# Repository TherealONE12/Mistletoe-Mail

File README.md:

# Mistletoe Mail

A Christmas Eve memory game for the [Holiday Hardware Swap](https://swap.hackclub.com/). Watch the bakery, post office and toy shop windows light up, then ring their doorbells in the same order. The route grows from two stops to six. Finish it to hear *Jingle Bells*.

## Play

- **Start a delivery:** Plug in USB and tap any doorbell. When all three windows glow dimly, repeat the route. A wrong turn replays it.
- **Quiet mode:** While idle, hold POST for a second and release to toggle sound on and off.
- **Music box:** Hold BAKERY and TOYS while plugging in, then release. The doors play C, E and G as notes.

## Hack it

On a Pico H running CircuitPython, copy [code.py](firmware/code.py) onto `CIRCUITPY`. Edit `CAROL` to edit the victory tune.

| Connection | Pico pins |
| --- | --- |
| Windows / doorbells, left to right | GP2, GP6, GP10 / GP4, GP8, GP12 |
| Piezo | GP14 |
| J1 expansion, top to bottom | 3V3, GP20 (SDA), GP21 (SCL), GND |

J1 accepts a 3.3 V I²C accessory with its own pull-ups.

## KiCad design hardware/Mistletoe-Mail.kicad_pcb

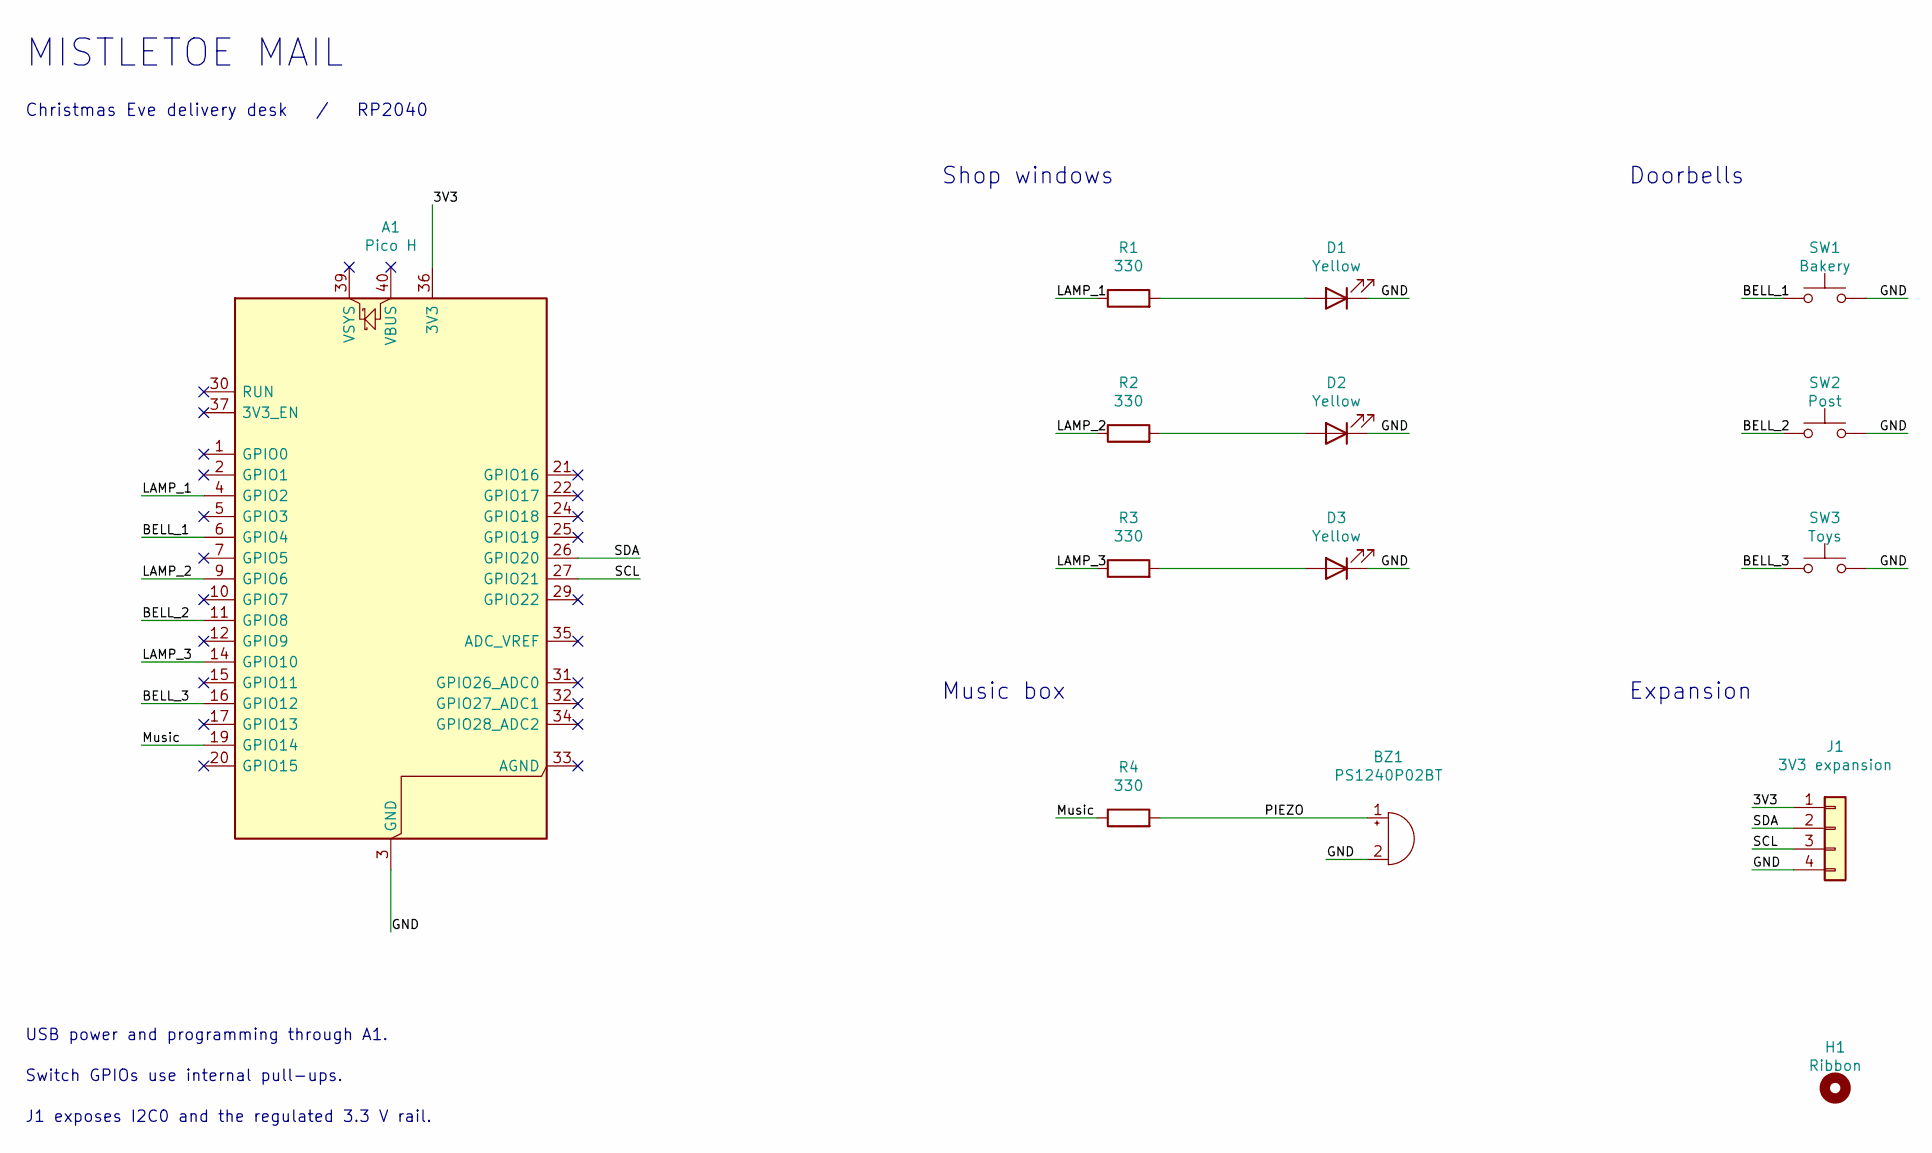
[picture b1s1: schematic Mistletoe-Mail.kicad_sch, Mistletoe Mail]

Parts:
A1: Pico H; Pico
BZ1: PS1240P02BT; Piezo
D1, D2, D3: Yellow; Window
H1: Ribbon; Eyelet
J1: 3V3 expansion; Port
R1, R2, R3, R4: 330; Resistor
SW1: Bakery; Doorbell
SW2: Post; Doorbell
SW3: Toys; Doorbell

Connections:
/3V3: A1.36 (3V3), J1.1
/ANODE_1: D1.2 (A), R1.2
/ANODE_2: D2.2 (A), R2.2
/ANODE_3: D3.2 (A), R3.2
/BELL_1: A1.6 (GPIO4), SW1.1
/BELL_2: A1.11 (GPIO8), SW2.1
/BELL_3: A1.16 (GPIO12), SW3.1
/CHIME: A1.19 (GPIO14), R4.1
/GND: A1.3 (GND), A1.8 (GND), A1.13 (GND), A1.18 (GND), A1.23 (GND), A1.28 (GND), A1.38 (GND), BZ1.2 (-), D1.1 (K), D2.1 (K), D3.1 (K), J1.4, SW1.2, SW2.2, SW3.2
/LAMP_1: A1.4 (GPIO2), R1.1
/LAMP_2: A1.9 (GPIO6), R2.1
/LAMP_3: A1.14 (GPIO10), R3.1
/PIEZO: BZ1.1 (+), R4.2
/SCL: A1.27 (GPIO21), J1.3
/SDA: A1.26 (GPIO20), J1.2

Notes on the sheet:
MISTLETOE MAIL
Christmas Eve delivery desk / RP2040
Expansion
Doorbells
Shop windows
USB power and programming through A1.
J1 exposes I2C0 and the regulated 3.3 V rail.
Music box
Switch GPIOs use internal pull-ups.

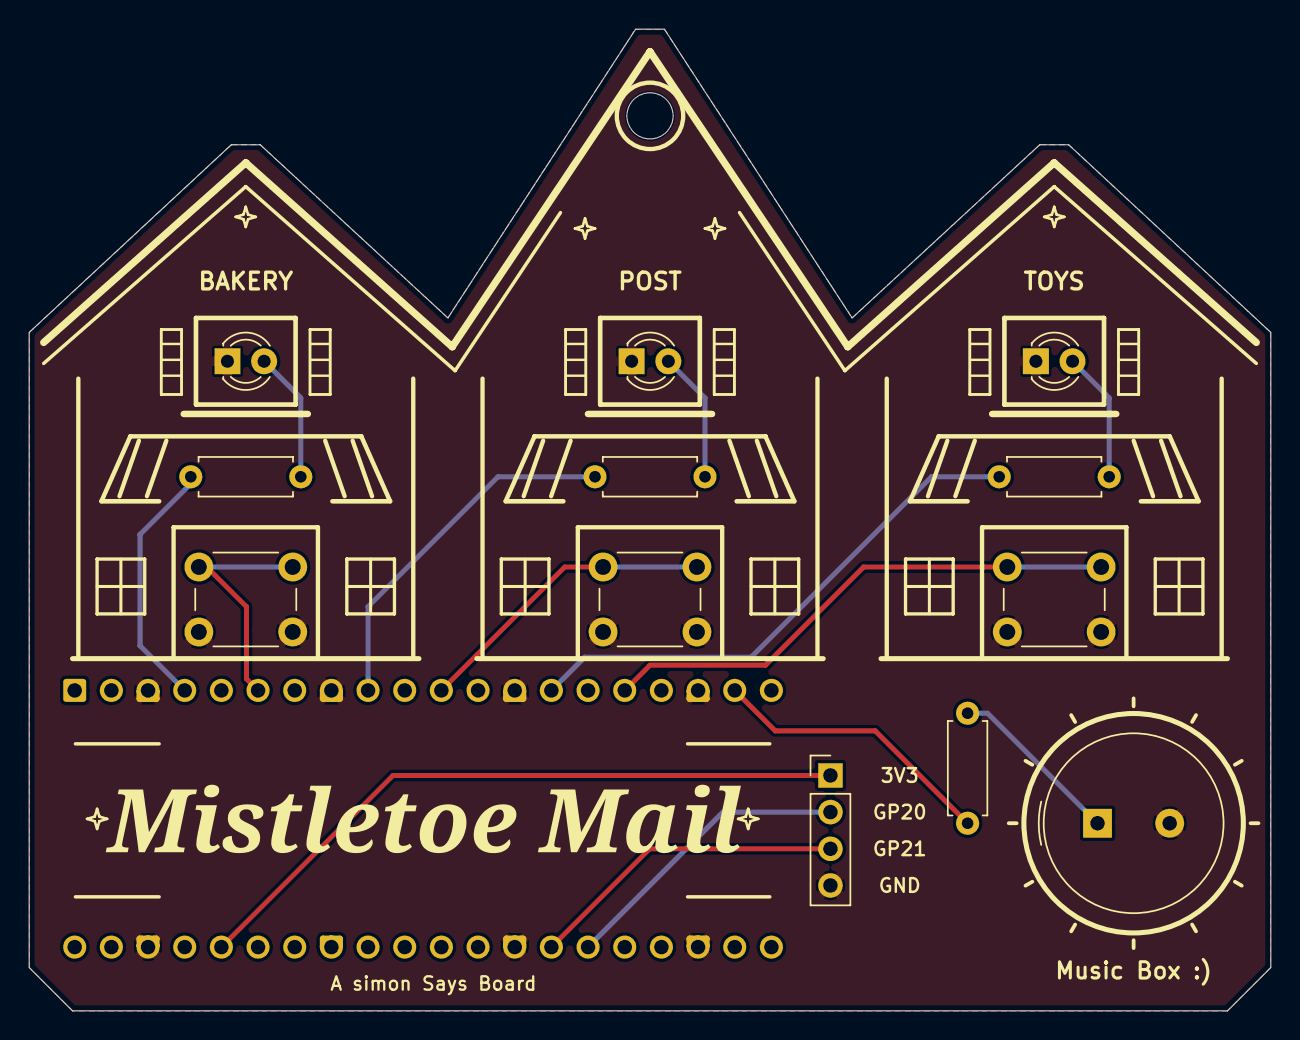
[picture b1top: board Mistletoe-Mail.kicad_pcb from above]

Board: 2 copper layers, 86.0 x 68.0 mm, 14 parts (1 on the bottom side), 15 nets.

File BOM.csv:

reference,part,order_quantity,unit,unit_USD,line_USD,source,notes
PCB,Mistletoe Mail r1,1,lot of five,2.00,2.00,https://jlcpcb.com/ads/pcb-prototype,Starting price for standard two-layer FR-4. Upload gerbers.zip for actual quote
A1,Raspberry Pi Pico H SC0917,5,each,5.00,25.00,https://www.digikey.com/en/products/detail/raspberry-pi/SC09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,RP2040 with factory headers. Solder directly to back
SW1 SW2 SW3,Omron B3F-1000,15,each,0.299,4.49,https://www.digikey.com/en/products/detail/aratas-formerly-o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,Normally open 6 x 6 mm through-hole switch with 4.3 mm actuator
D1 D2 D3,Kingbright WP710A10LYD,15,each,0.173,2.60,https://www.digikey.com/en/products/detail/kingbright/WP710A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,Low-current yellow 3 mm LED with 2.54 mm lead spacing
R1 R2 R3 R4,Stackpole CF14JT330R,20,each,0.027,0.54,https://www.digikey.com/en/products/detail/stackpole-electro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,330 ohms 0.25 W axial. Form leads for 7.62 mm pitch
BZ1,TDK PS1240P02BT,5,each,0.67,3.35,https://www.digikey.com/en/products/detail/tdk-corporation/P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,Externally driven piezo. 12.2 mm diameter with 5 mm pitch
USB,Monoprice 5137 USB-A to Micro-B,5,each,1.19,5.95,https://www.monoprice.com/product?p_id=5137,1.5 ft power and data cable for each recipient or keeper
Gift materials,Paper and ribbon,1,batch,1.00,1.00,,Allowance for cards and hanging loops
Reserve,Inbound freight tax and price changes,1,batch,20.00,20.00,,Planning allowance across the orders. Actual checkout varies by destination
